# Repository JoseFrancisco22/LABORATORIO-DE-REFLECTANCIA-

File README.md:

# LABORATORIO-DE-REFLECTANCIA-
Código para controlar el sistema de medición de espectros de reflectancia diferencial (RDS) en el laboratorio de reflectancia.

## Introducción
Este repositorio contiene el código desarrollado en el laboratorio de reflectancia para adquirir y procesar espectros de Reflectancia Diferencial (RDS). El sistema se utiliza para caracterizar anisotropías ópticas en superficies y heteroestructuras semiconductoras, complementando las mediciones de fotoluminiscencia.

## Funcionalidades principales
- Control de monocromador
- Adquisición síncrona con voltimetro el lock-in amplifier
- Barrido automático de longitud de onda
- Cálculo en tiempo real de la señal RDS.

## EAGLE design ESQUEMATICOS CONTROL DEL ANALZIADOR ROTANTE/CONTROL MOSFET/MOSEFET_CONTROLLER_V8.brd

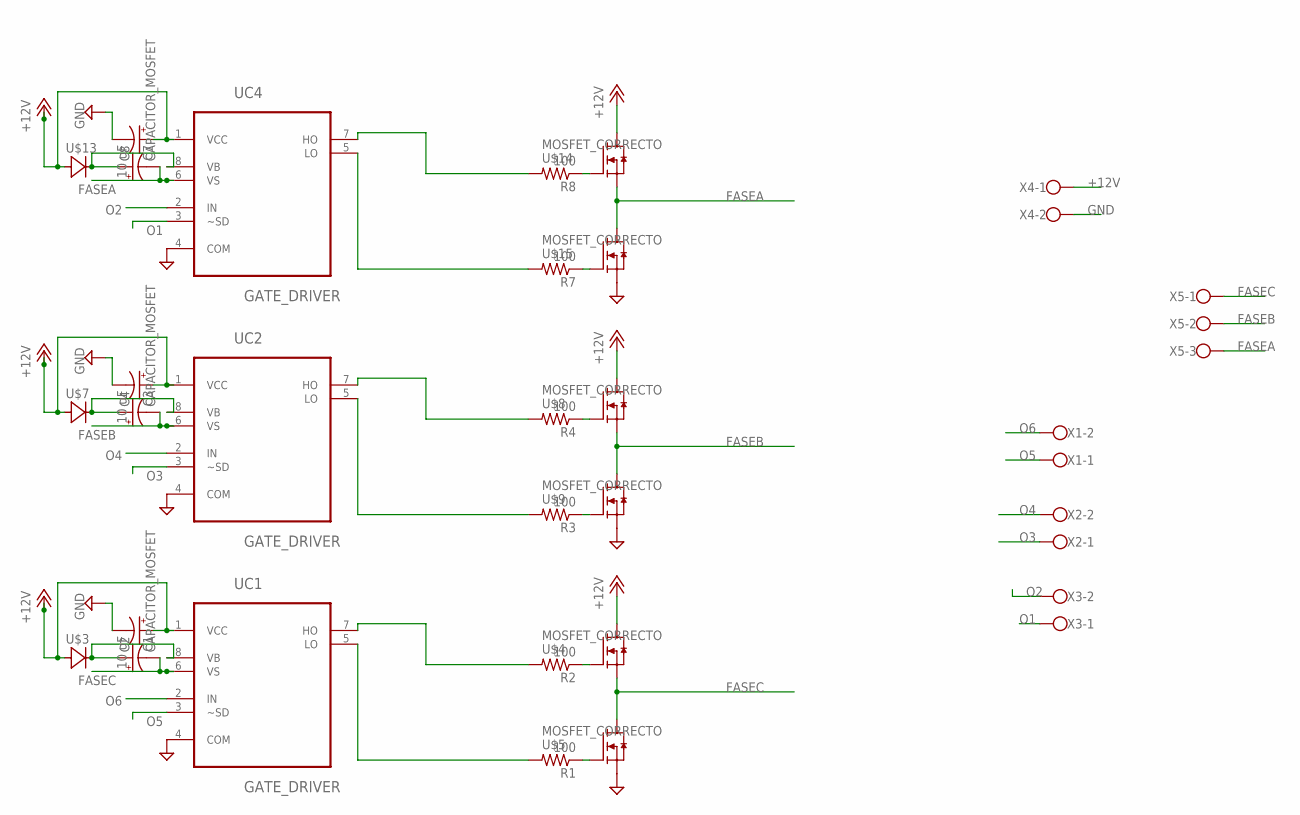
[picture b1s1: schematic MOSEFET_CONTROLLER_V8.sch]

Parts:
C1, C3, C7: 10 uF; 153CLV-0505
C2, C4, C8: CAPACITOR_MOSFET; E2,5-5
R1, R2, R3, R4, R7, R8: 100; R1206
U$3, U$7, U$13: DIODO_SMD; DO214AC
U$4, U$5, U$8, U$9, U$14, U$15: MOSFET_CORRECTO; MOSFET_BUENO
UC1, UC2, UC4: GATE_DRIVER
X1, X2, X3, X4: W237-102
X5: W237-103

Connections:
+12V: C1.+, C3.+, C7.+, U$3.A, U$4.3 (D), U$7.A, U$8.3 (D), U$13.A, U$14.3 (D), UC1.1 (VCC), UC2.1 (VCC), UC4.1 (VCC), X4.1
FASEA: C8.-, U$14.2 (S), U$15.3 (D), UC4.6 (VS), X5.3
FASEB: C4.-, U$8.2 (S), U$9.3 (D), UC2.6 (VS), X5.2
FASEC: C2.-, U$4.2 (S), U$5.3 (D), UC1.6 (VS), X5.1
GND: C1.-, C3.-, C7.-, U$5.2 (S), U$9.2 (S), U$15.2 (S), UC1.4 (COM), UC2.4 (COM), UC4.4 (COM), X4.2
unnamed: R1.2, UC1.5 (LO)
unnamed: R2.2, UC1.7 (HO)
unnamed: R1.1, U$5.1 (G)
unnamed: R2.1, U$4.1 (G)
unnamed: C2.+, U$3.C, UC1.8 (VB)
unnamed: R3.2, UC2.5 (LO)
unnamed: R4.2, UC2.7 (HO)
unnamed: R3.1, U$9.1 (G)
unnamed: R4.1, U$8.1 (G)
unnamed: C4.+, U$7.C, UC2.8 (VB)
unnamed: R7.2, UC4.5 (LO)
unnamed: R8.2, UC4.7 (HO)
unnamed: R7.1, U$15.1 (G)
unnamed: R8.1, U$14.1 (G)
unnamed: C8.+, U$13.C, UC4.8 (VB)
O1: UC4.3 (~SD), X3.1
O2: UC4.2 (IN), X3.2
O3: UC2.3 (~SD), X2.1
O4: UC2.2 (IN), X2.2
O5: UC1.3 (~SD), X1.1
O6: UC1.2 (IN), X1.2

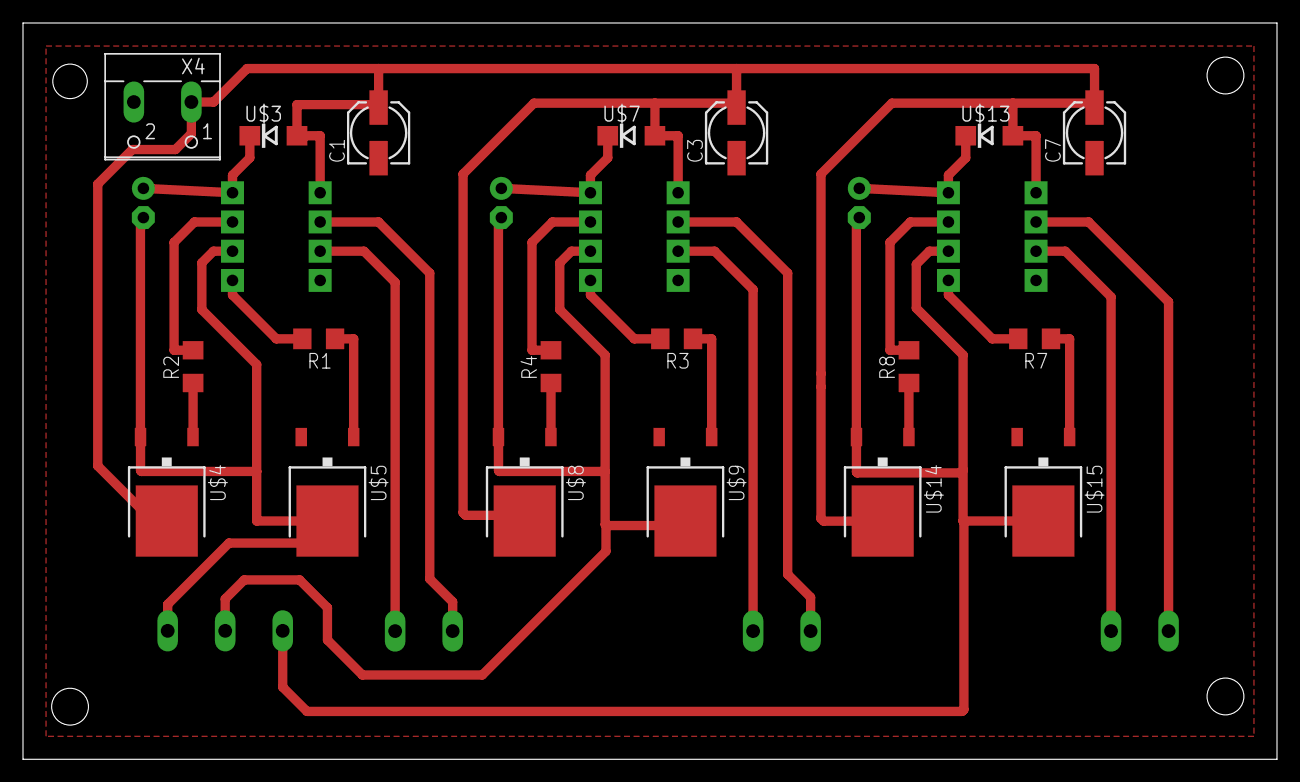
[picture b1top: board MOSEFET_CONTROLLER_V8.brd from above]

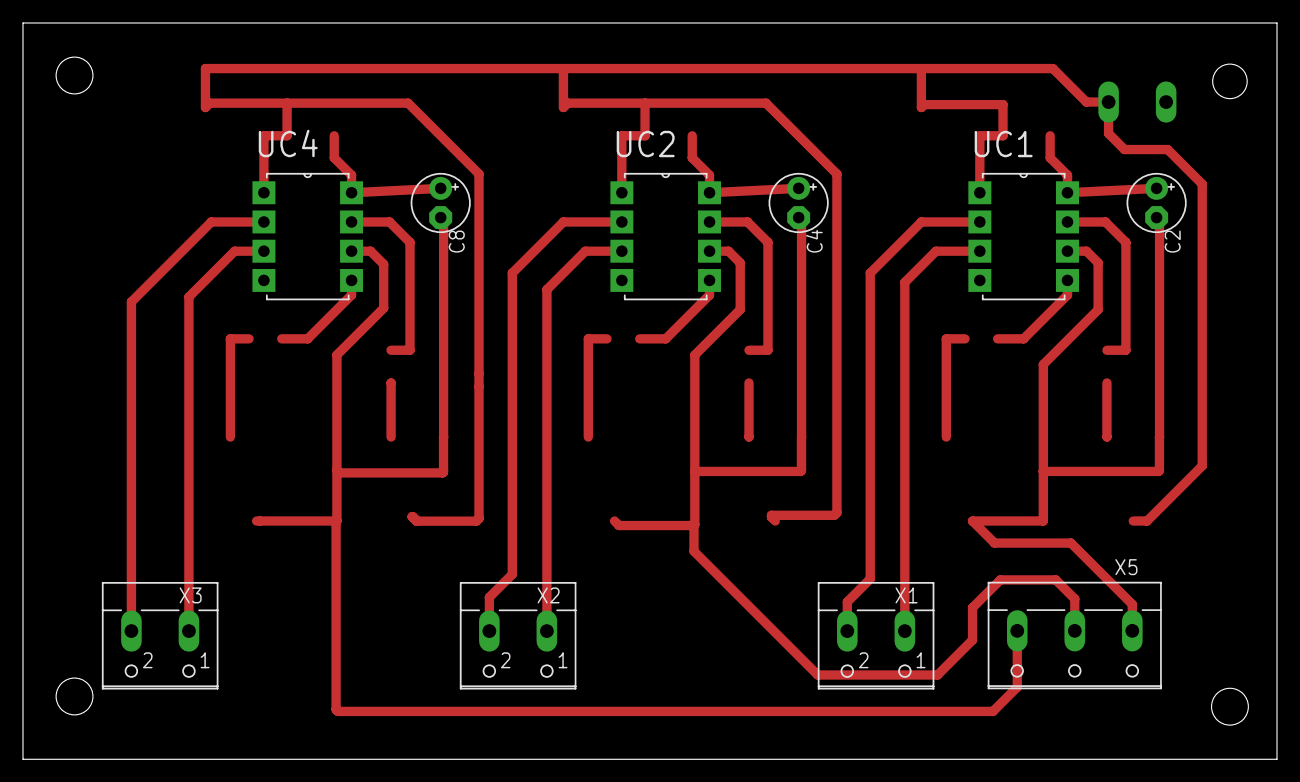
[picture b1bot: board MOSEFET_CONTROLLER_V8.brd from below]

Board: 2 copper layers, 109.0 x 64.0 mm, 29 parts (10 on the bottom side), 26 nets.

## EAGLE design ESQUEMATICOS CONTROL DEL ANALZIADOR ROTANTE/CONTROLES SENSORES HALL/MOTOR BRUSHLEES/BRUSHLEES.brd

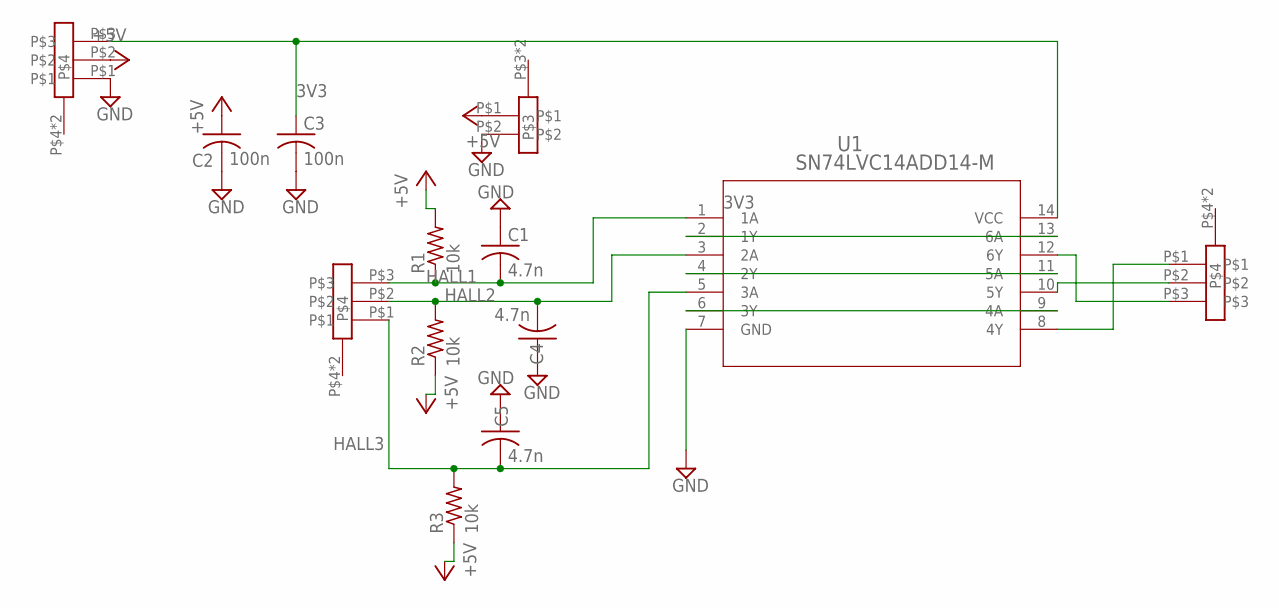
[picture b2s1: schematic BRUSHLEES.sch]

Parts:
ALIMENTACION: PH3
BORN3: PH3
C1, C4, C5: 4.7n; C1206K
C2, C3: 100n; C1206K
EXT: PH3
R1, R2, R3: 10k; R1206
U1: SN74LVC14ADD14-M; D14-M
U$1: PH2

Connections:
3V3: ALIMENTACION.P$3, C3.1, U1.14 (VCC)
+5V: ALIMENTACION.P$2, C2.1, R1.2, R2.1, R3.1, U$1.P$1
GND: ALIMENTACION.P$1, C1.1, C2.2, C3.2, C4.1, C5.1, U1.7 (GND), U$1.P$2
HALL1: BORN3.P$3, C1.2, R1.1, U1.1 (1A)
HALL2: BORN3.P$2, C4.2, R2.2, U1.3 (2A)
HALL3: BORN3.P$1, C5.2, R3.2, U1.5 (3A)
unnamed: U1.4 (2Y), U1.11 (5A)
unnamed: U1.2 (1Y), U1.13 (6A)
unnamed: U1.6 (3Y), U1.9 (4A)
unnamed: EXT.P$1, U1.8 (4Y)
unnamed: EXT.P$2, U1.10 (5Y)
unnamed: EXT.P$3, U1.12 (6Y)

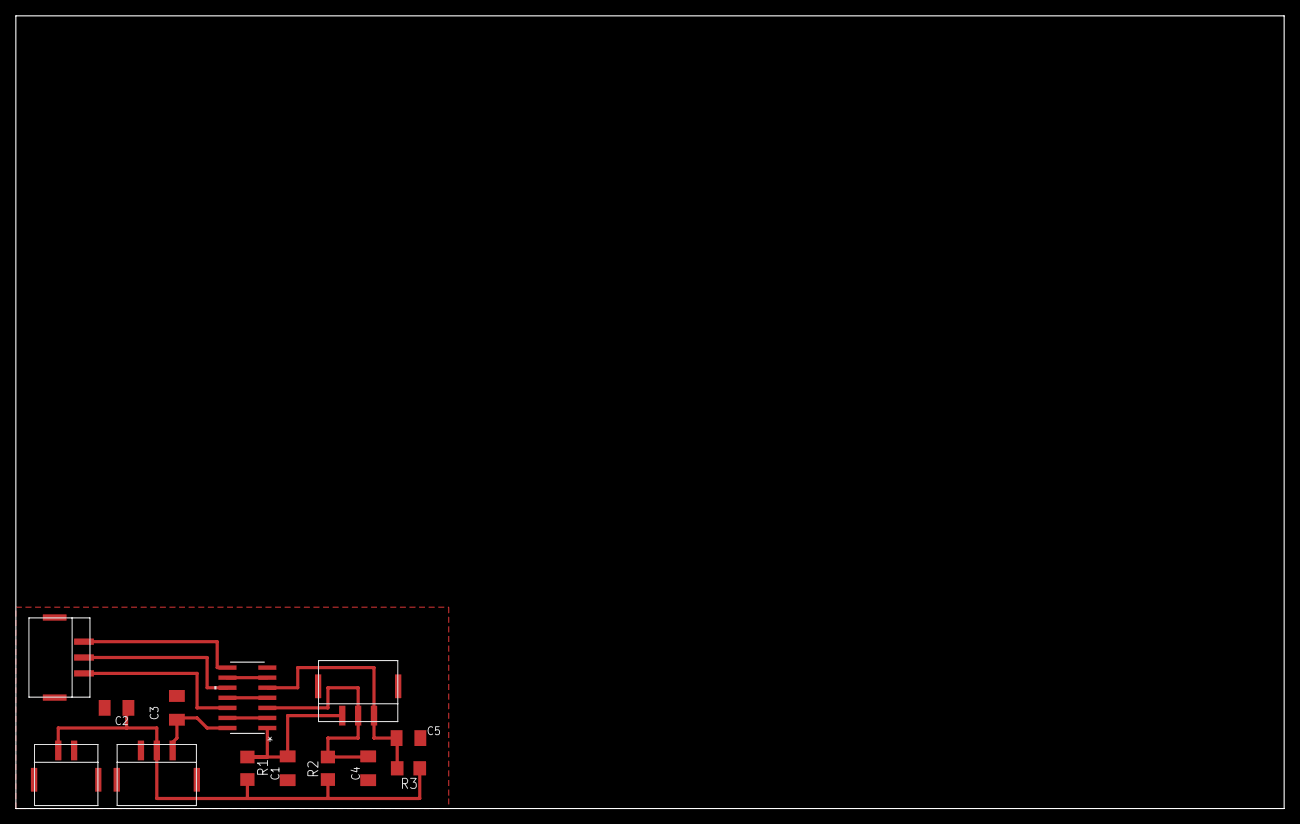
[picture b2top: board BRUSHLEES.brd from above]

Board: 2 copper layers, 160.0 x 100.0 mm, 13 parts (0 on the bottom side), 12 nets.

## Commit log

2026-04-16 README.md
2026-04-16 Monocromador.py
2026-04-16 Control_LockIn.py
2026-04-16 Control_voltimetro.py
2026-04-16 Reflectancia_Diferencial.py

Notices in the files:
parts and their libraries:
COPYRIGHT: Copyright (C) 2024 Ultra Librarian. All rights reserved.
